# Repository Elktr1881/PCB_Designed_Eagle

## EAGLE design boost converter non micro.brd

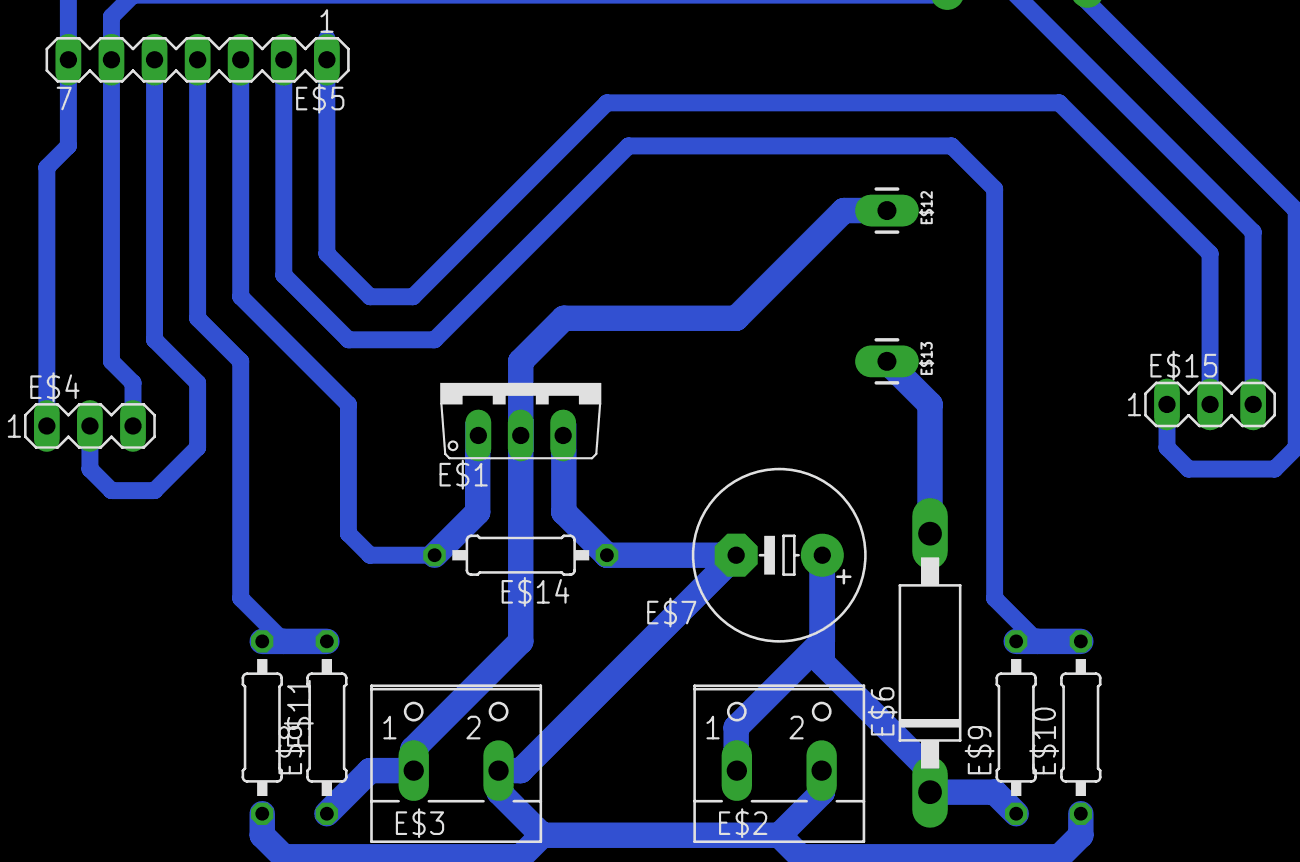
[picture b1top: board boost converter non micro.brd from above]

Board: 2 copper layers, 15 parts (0 on the bottom side), 9 nets.

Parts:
E$1: T-30_V
E$2, E$3: W237-102
E$4, E$15: MA03-1
E$5: MA07-1
E$6: CB417-15
E$7: E5-10,5
E$8, E$9, E$10, E$11, E$14: 0207/10
E$12, E$13: 1X01_LONGPAD

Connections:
S$1: E$4.1, E$5.7, E$15.3
S$3: E$5.4, E$8.2, E$11.1
S$5: E$4.3, E$5.6
S$6: E$6.C, E$7.+, E$9.1
S$7: E$6.A, E$13.1
S$8: E$8.1, E$12.1
S$9: E$7.-, E$10.1, E$11.2, E$14.1
S$10: E$4.2, E$5.5
S$12: E$5.2, E$5.3, E$9.2, E$10.2, E$14.2

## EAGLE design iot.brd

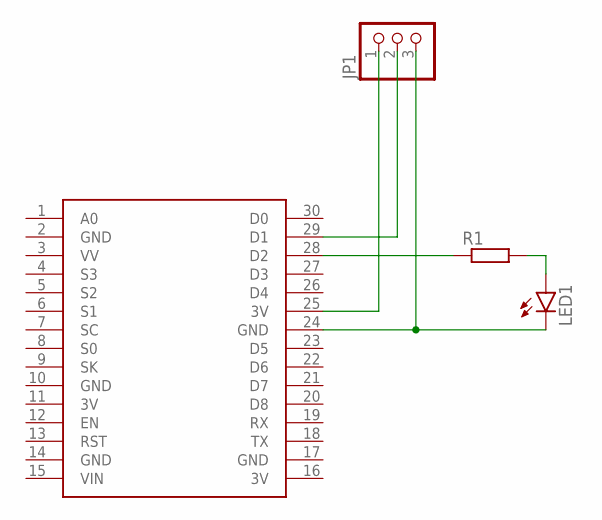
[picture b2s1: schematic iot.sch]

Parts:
JP1: PINHD-1X3; 1X03
LED1: LED3MM
R1: R-EU_0207/7; 0207/7
U$1: NODEMCU

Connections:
3V: U$1.11 (3V), U$1.16 (3V)
GND: U$1.2 (GND), U$1.10 (GND), U$1.14 (GND), U$1.17 (GND)
unnamed: JP1.2, U$1.29 (D1)
unnamed: JP1.3, LED1.K (C), U$1.24 (GND)
unnamed: JP1.1, U$1.25 (3V)
unnamed: R1.1, U$1.28 (D2)
unnamed: LED1.A, R1.2

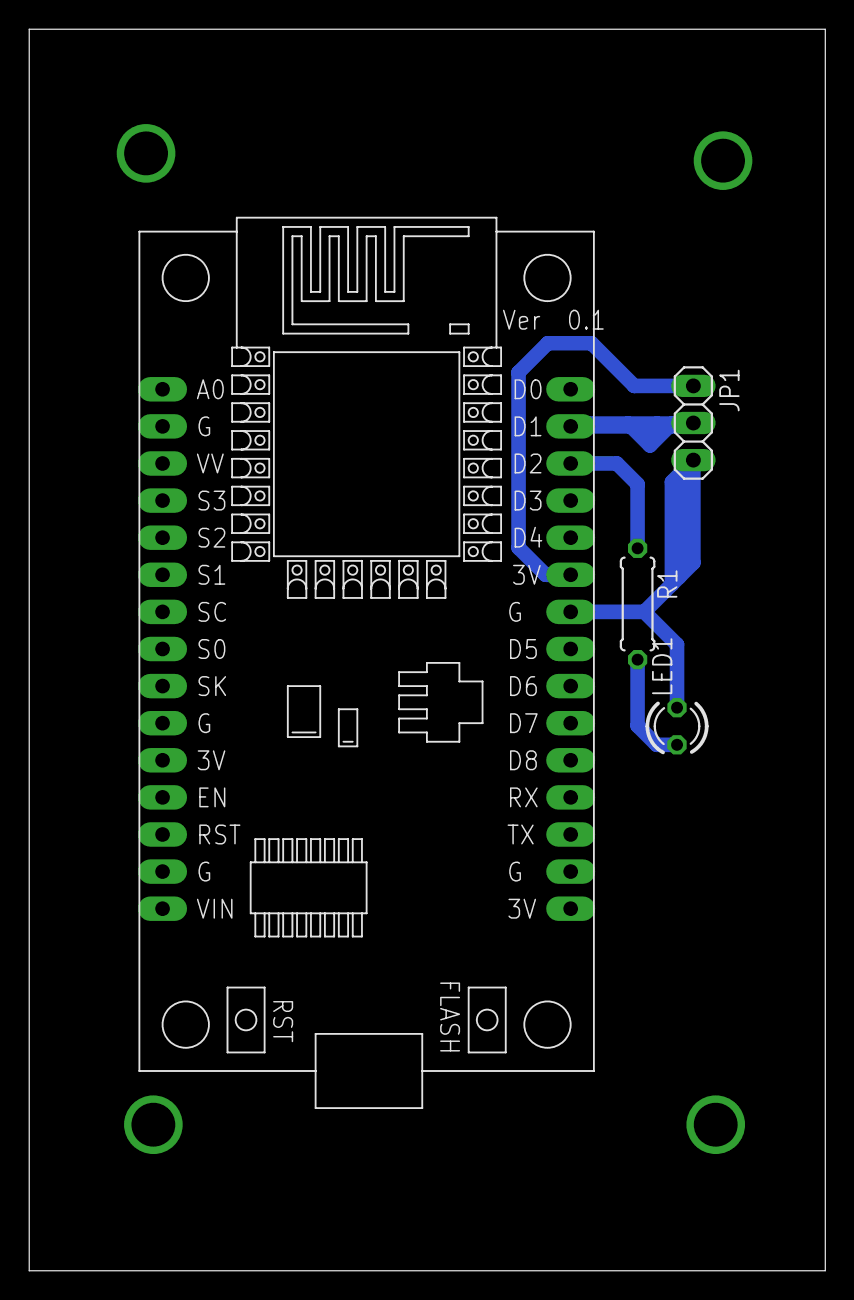
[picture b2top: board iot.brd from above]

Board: 2 copper layers, 54.5 x 85.0 mm, 4 parts (0 on the bottom side), 7 nets.

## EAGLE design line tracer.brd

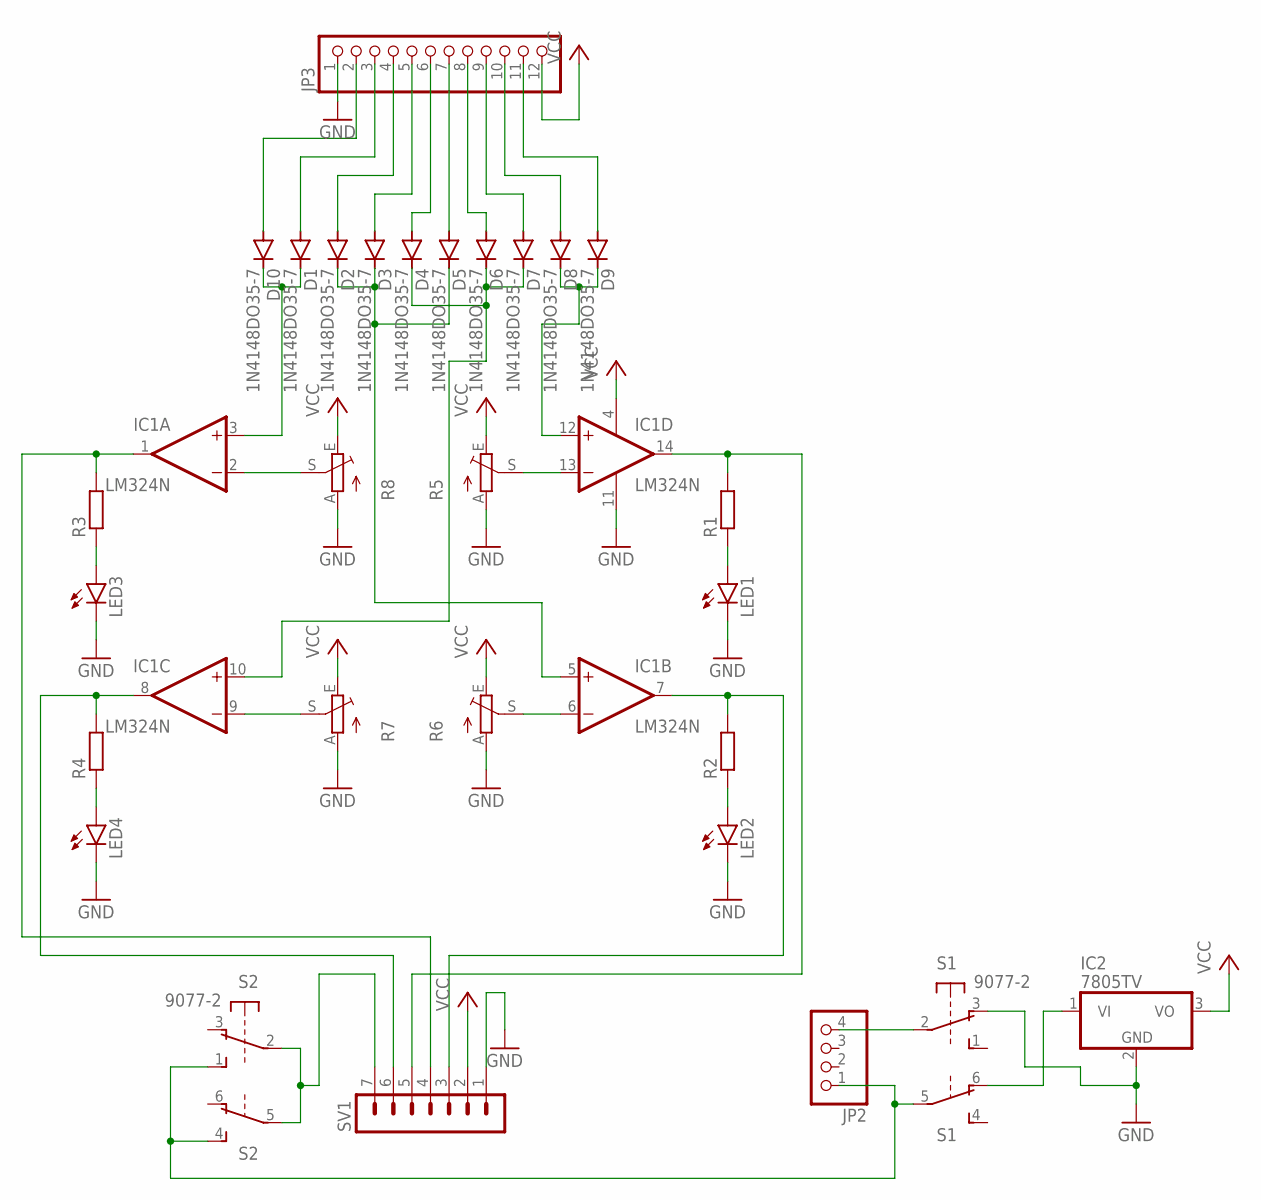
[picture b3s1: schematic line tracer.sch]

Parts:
D1, D2, D3, D4, D5, D6, D7, D8, D9, D10: 1N4148DO35-7; DO35-7
IC1: LM324N; DIL14
IC2: 7805TV; TO220V
JP2: PINHD-1X4; 1X04
JP3: PINHD-1X12; 1X12
LED1, LED2, LED3, LED4: LED3MM
R1, R2, R3, R4: R-EU_0207/7; 0207/7
R5, R6, R7, R8: TRIM_EU-CA6V; CA6V
S1, S2: 9077-2
SV1: MA07-1

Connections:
GND: IC1.11 (V-), IC2.2 (GND), JP3.1, LED1.K (C), LED2.K (C), LED3.K (C), LED4.K (C), R5.A, R6.A, R7.A, R8.A, S1.3 (O), SV1.1
unnamed: IC1.13 (-IN), R5.S
unnamed: IC1.2 (-IN), R8.S
unnamed: IC1.9 (-IN), R7.S
unnamed: IC1.6 (-IN), R6.S
unnamed: IC1.7 (OUT), R2.2, SV1.3
unnamed: LED2.A, R2.1
unnamed: LED1.A, R1.1
unnamed: IC1.14 (OUT), R1.2, SV1.5
unnamed: IC1.8 (OUT), R4.2, SV1.6
unnamed: LED3.A, R3.1
unnamed: LED4.A, R4.1
unnamed: JP2.4, S1.2
unnamed: JP2.1, S1.5, S2.1 (S), S2.4 (S)
unnamed: IC2.1 (VI), S1.6 (O)
unnamed: D10.A, JP3.2
unnamed: D1.C, D10.C, IC1.3 (+IN)
unnamed: D8.C, D9.C, IC1.12 (+IN)
unnamed: D2.C, D3.C, D5.C, IC1.5 (+IN)
unnamed: S2.2, S2.5, SV1.7
unnamed: D1.A, JP3.3
unnamed: D2.A, JP3.4
unnamed: D3.A, JP3.5
unnamed: D4.A, JP3.6
unnamed: IC1.1 (OUT), R3.2, SV1.4
unnamed: D5.A, JP3.7
unnamed: D6.A, JP3.8
unnamed: D7.A, JP3.9
unnamed: D8.A, JP3.10
unnamed: D9.A, JP3.11
unnamed: D4.C, D6.C, D7.C, IC1.10 (+IN)
VCC: IC1.4 (V+), IC2.3 (VO), JP3.12, R5.E, R6.E, R7.E, R8.E, SV1.2

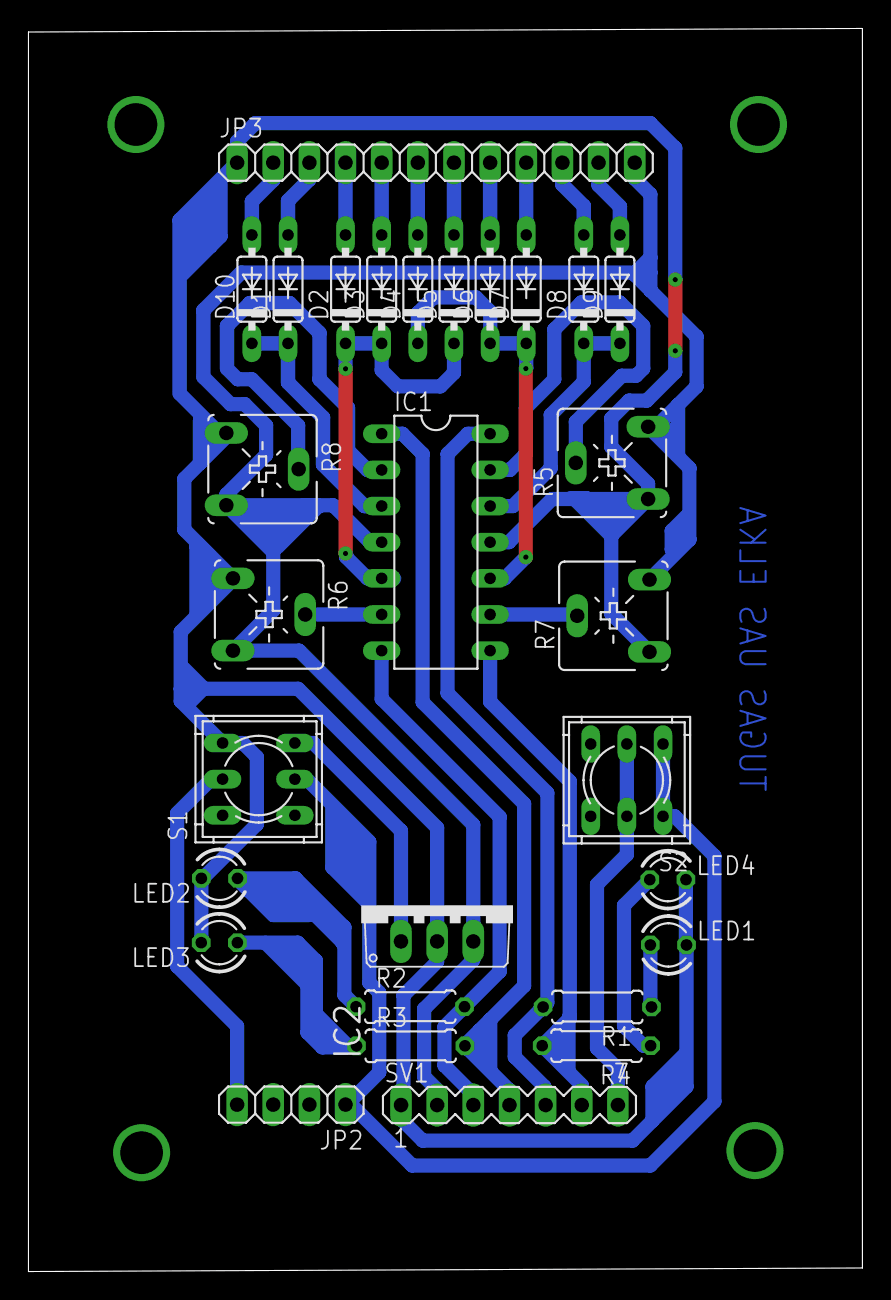
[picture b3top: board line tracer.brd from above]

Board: 2 copper layers, 58.6 x 87.4 mm, 29 parts (0 on the bottom side), 32 nets.

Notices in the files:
parts and their libraries:
SparkFun-Connectors: Licensing: Creative Commons ShareAlike 4.0 International - https://creativecommons.org/licenses/by-sa/4.0
